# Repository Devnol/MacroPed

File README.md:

# MacroPed
Put your lower limbs to use with this Rpi Pico-powered macropad

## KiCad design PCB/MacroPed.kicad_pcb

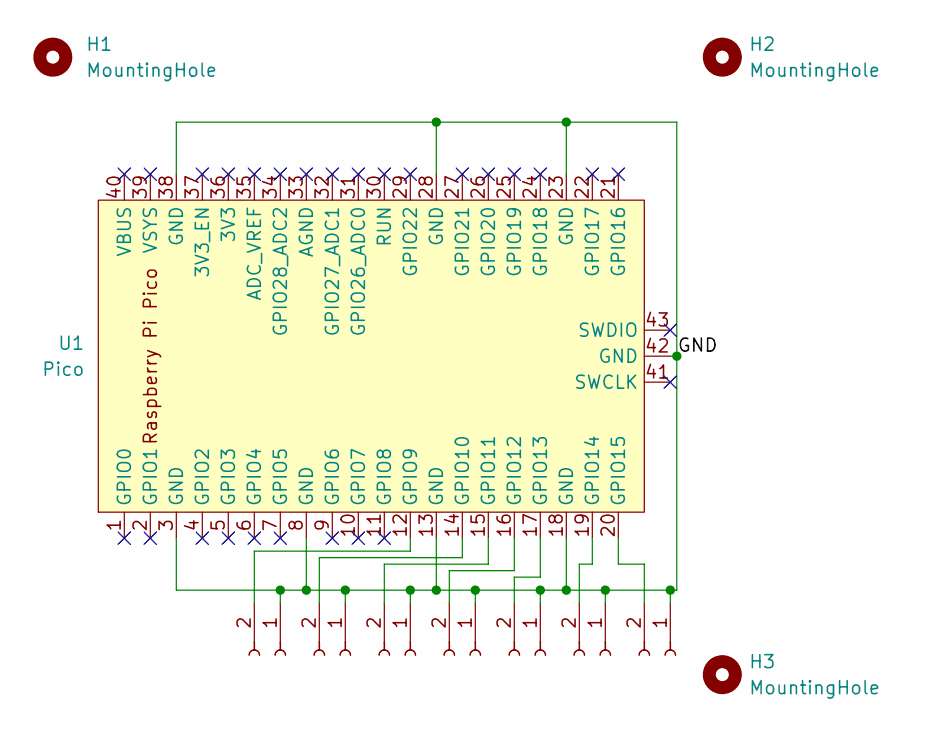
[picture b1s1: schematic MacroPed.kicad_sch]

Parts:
H1, H2, H3: MountingHole; MountingHole_2.7mm_M2.5_DIN965
J1, J2, J3, J4, J5, J6, J7: Conn_01x02_Socket; JST_PH_S2B-PH-K_1x02_P2.00mm_Horizontal
U1: Pico; RPi_Pico_SMD_TH

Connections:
/GND: J1.1, J2.1, J3.1, J4.1, J5.1, J6.1, J7.1, U1.3 (GND), U1.8 (GND), U1.13 (GND), U1.18 (GND), U1.23 (GND), U1.28 (GND), U1.38 (GND), U1.42 (GND)
unnamed: J1.2, U1.12 (GPIO9)
unnamed: J2.2, U1.14 (GPIO10)
unnamed: J3.2, U1.15 (GPIO11)
unnamed: J4.2, U1.16 (GPIO12)
unnamed: J5.2, U1.17 (GPIO13)
unnamed: J6.2, U1.19 (GPIO14)
unnamed: J7.2, U1.20 (GPIO15)

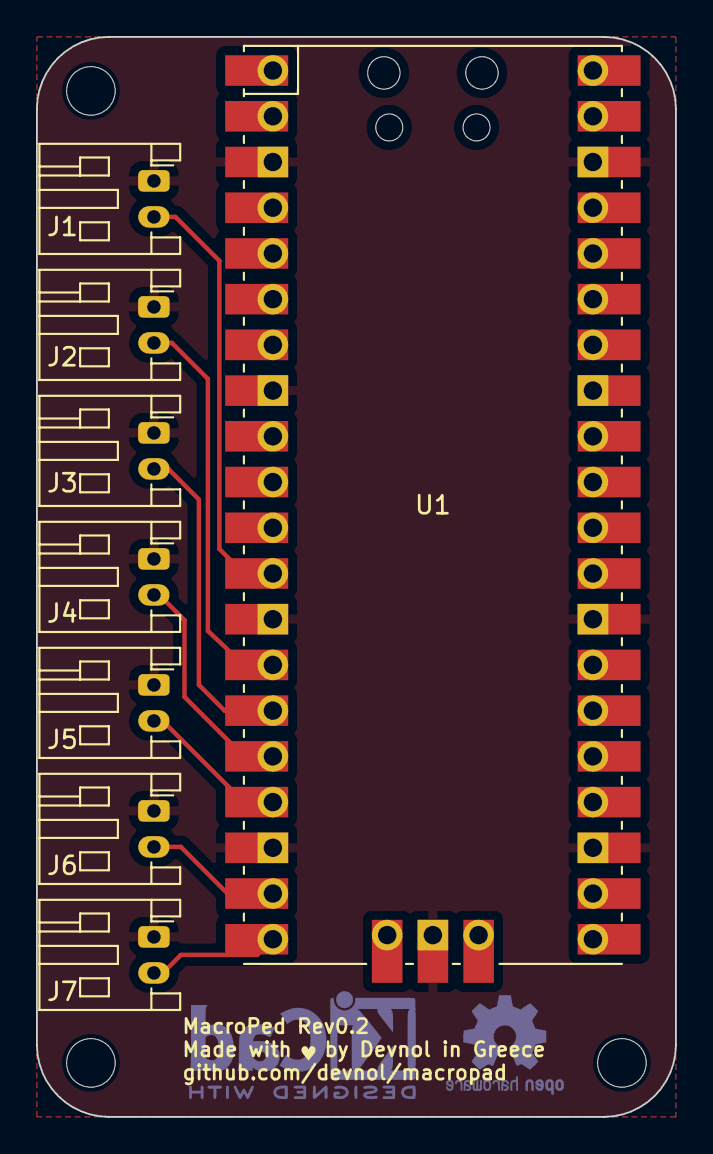
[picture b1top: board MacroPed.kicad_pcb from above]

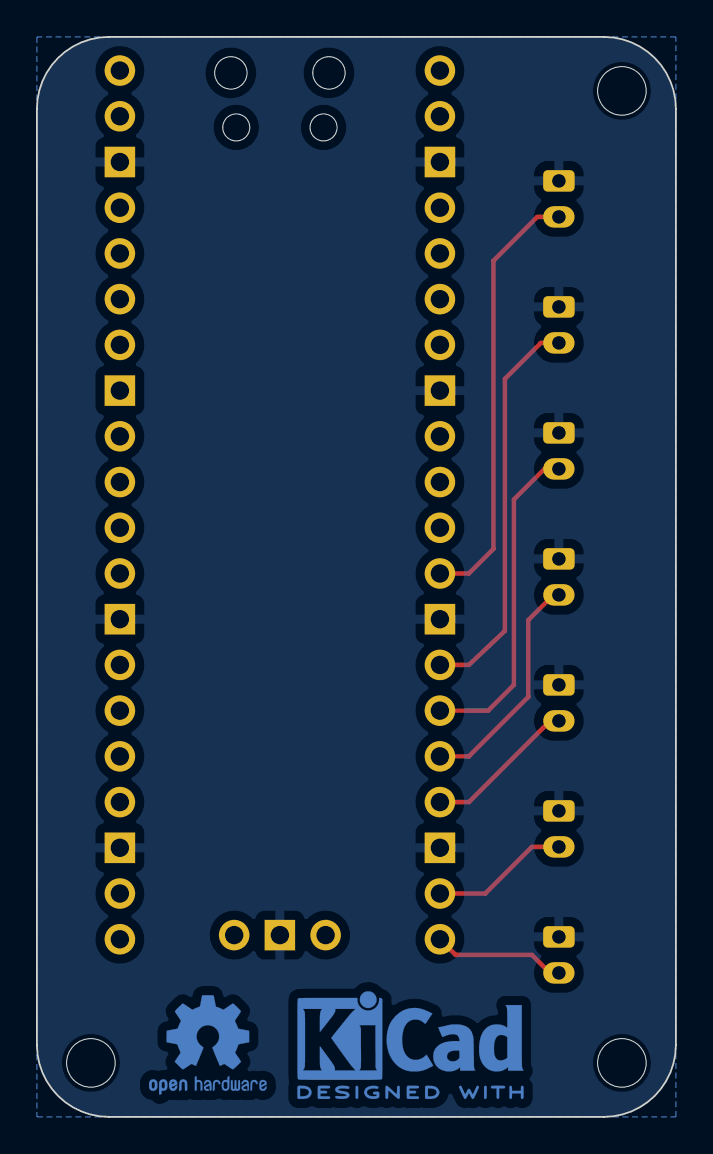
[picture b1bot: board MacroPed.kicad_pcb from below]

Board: 2 copper layers, 35.5 x 60.0 mm, 13 parts (2 on the bottom side), 8 nets.

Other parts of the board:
Logo1: OSHW-Logo2_7.3x6mm_Copper
Logo2: KiCad-Logo2_5mm_Copper

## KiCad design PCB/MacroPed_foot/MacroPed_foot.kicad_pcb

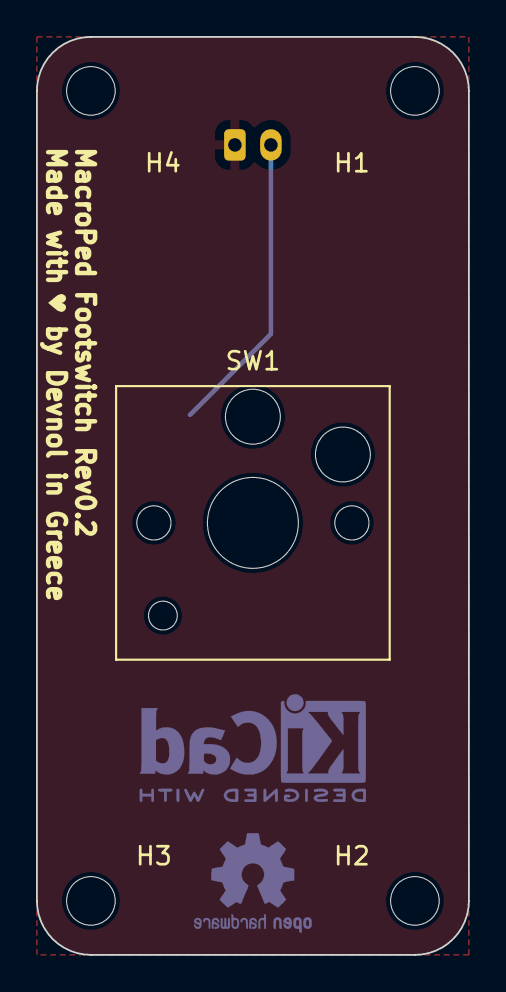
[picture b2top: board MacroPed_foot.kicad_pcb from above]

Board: 2 copper layers, 24.0 x 51.0 mm, 6 parts (1 on the bottom side), 2 nets.

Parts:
H1, H2, H3, H4: MountingHole; MountingHole_2.7mm_M2.5_DIN965
J1: Conn_01x02_Socket; JST_PH_S2B-PH-K_1x02_P2.00mm_Horizontal
SW1: SW_SPST; SW_Hotswap_Kailh_Choc_V1V2_2.00u_90deg

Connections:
/Foot_GND: J1.1, SW1.2 (B)
unnamed: J1.2, SW1.1 (A)

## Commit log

2023-06-18 Added schematic and pcb model
2023-06-18 Add TAPR OHL
2023-06-18 Moved PCB designs to subfolder
2023-06-18 Separated daughterboard to sub-project, added mounting holes
2023-06-27 Move jst to back of pedal to save on SMT
2023-06-28 Move connectors to one side, change dimensions to proper units
2023-06-28 Change board dimensions to real units
2023-06-28 add production files
2023-07-21 Moved JST connector to edge of footboard
2023-07-21 Shorten main board
2023-08-08 Initial code commit
2024-07-11 Added CAD models for enclosures
2024-07-11 Fanned out pedal switches
2024-07-11 Fanned out pedals and created plates to join them together
2024-07-12 Added padding to joining plates
2024-07-12 (feat): added ability to change keymap or reset board without unplugging (feat): added delays between macro keystrokes (refactor): minor fixupping from last year's codebase
2024-07-13 Cut cable guide under pedal joiner plates Add button and LED hole on pico case
2024-07-14 Update adafruit_hid
2024-07-14 Reorder functions, add led feedback on menu
2024-07-15 Added some keymaps for vscode and fusion360
2024-07-15 Complete F360 keymap, improve blinking feedback
2024-07-16 Add mappings for general macOS navigation and firefox browsing.
